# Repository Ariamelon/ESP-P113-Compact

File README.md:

# ESP-P113
 Compact version of ESP's Project 113 Amplifier done with SMT resistors and ceramic caps. PSU idea taken from https://theslowdiyer.wordpress.com/2019/09/10/project-files-filtered-irm-power-supplies-part-1/. Designed to go in sideways in this case (https://item.taobao.com/item.htm?id=54329725614). 

 ## Changelog
 ### V1
* 25/05/2021: Initial commit.
* 26/05/2021: Updated to V1.1. Added primary-side fuse, changed inductor to cheaper variant and rearranged components to make board even more compact. Updated BOM to match. Added extra M3 hole in middle of PCB and changed that hole to be the case grounding point instead.
* 27/05/2021: Updated to V1.2. Slightly changed position of transistors to allow for them to be mounted to an aluminium L-bracket and then to the case. 3mm power LEDs added. Changed output resistors to THT 0.5W versions. Added disclaimer on board. Moved position of components in CLC filter for more optimal routing.
 ### V2
* 29/05/2021: Updated to V2.0. A 220p compensation cap between opamp output and inverting input helped tame ringing on square waves with a 600R load with 10nF in parallel. A standard zobel network has also been added. Fixed major error with transistors (used wrong symbols/wrong way round, oops!). Added varistor between each power supply input and 3R resistor in series into live input, changed capacitor layout in output and added TVS diode to protect electronics in case converter fails as per CUI PSK-20D datasheet. 3.15A fuses into each live input will also be added off-board in the final design. Added gain switches to toggle gain resistance between 3k3 and 9k1 by switching 5k1 resistor in and out of parallel (actual resistance with both resistors in parallel is around 3k27, close enough), with option to choose between on-board DIP switches and off-board headers to use another switch. Output transistors changed to BD139/140. New layout, slightly larger but should still fit in planned case. Many thanks to user AnalogSteph on ASR for the help on the majority of the changes.
 ### V3
* 04/06/2021: Updated to V3.0. New layout with (hopefully) accurate measurements as drawings of case to be used have been received. Changed PSU to RAC20-15DK to save space and removed varistor. 200mA fuse will be used instead of 3.15A. Output BJTs changed to MJE15028/29s as they offer slightly better simulated distortion. The gain resistors have been changed to 560R/5k6 to allow for gain values of 1.5 and 6.6. PSU filter has been changed to CLC as that is more than adequate filtering. The DC protection and muting circuit from AMB has been added to protect the headphone out. On-board Y2 capacitor has been added for convenience. All SMT capacitors now also 1206 or 1210. Added 22kR/220pF RFI RC filter at the last second.

 ## Photos

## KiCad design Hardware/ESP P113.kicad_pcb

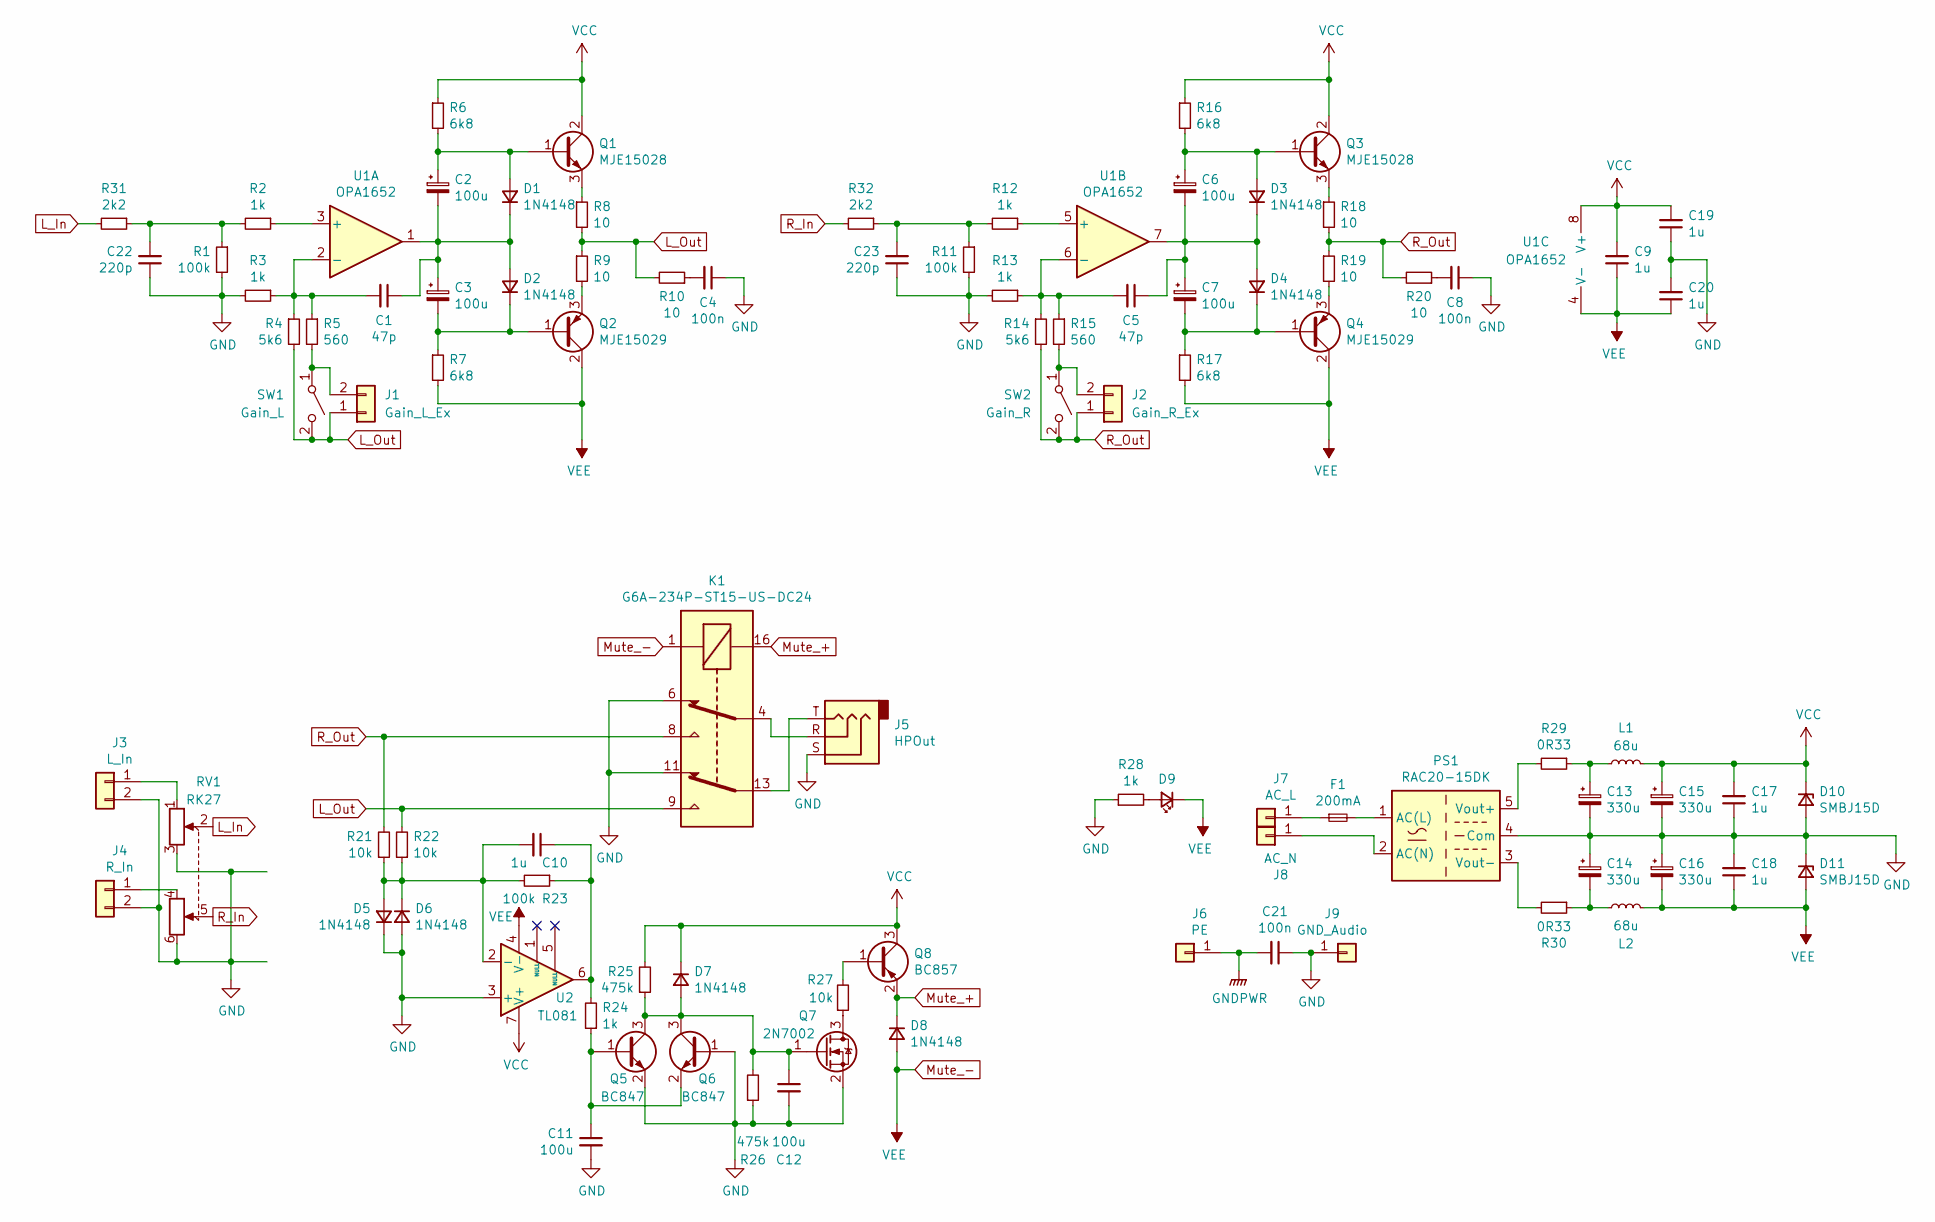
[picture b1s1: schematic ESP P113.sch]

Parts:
C1, C5: 47p; C_1206_3216Metric_Pad1.33x1.80mm_HandSolder
C2, C3, C6, C7: 100u; CP_Radial_D6.3mm_P2.50mm
C4, C8: 100n; C_1210_3225Metric_Pad1.33x2.70mm_HandSolder
C9, C17, C18, C19, C20: 1u; C_1206_3216Metric_Pad1.33x1.80mm_HandSolder
C10: 1u; C_Rect_L7.2mm_W5.5mm_P5.00mm_FKS2_FKP2_MKS2_MKP2
C11, C12: 100u; CP_Radial_D8.0mm_P3.50mm
C13, C14, C15, C16: 330u; CP_Radial_D8.0mm_P3.50mm
C21: 100n; C_Rect_L26.5mm_W8.5mm_P22.50mm_MKS4
C22, C23: 220p; C_1206_3216Metric_Pad1.33x1.80mm_HandSolder
D1, D2, D3, D4, D5, D6, D7, D8: 1N4148; D_SOD-123
D9: LED; LED_D3.0mm
D10, D11: SMBJ15D; D_SMB
F1: 200mA; Fuseholder_Cylinder-5x20mm_Schurter_0031_8201_Horizontal_Op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
J1: Gain_L_Ex; JST_XH_B2B-XH-A_1x02_P2.50mm_Vertical
J2: Gain_R_Ex; JST_XH_B2B-XH-A_1x02_P2.50mm_Vertical
J3: L_In; JST_XH_B2B-XH-A_1x02_P2.50mm_Vertical
J4: R_In; JST_XH_B2B-XH-A_1x02_P2.50mm_Vertical
J5: HPOut; Jack_6.35mm_Neutrik_NMJ6HCD2_Horizontal
J6: PE; FastOn
J7: AC_L; FastOn
J8: AC_N; FastOn
J9: GND_Audio; FastOn
K1: G6A-234P-ST15-US-DC24; Relay_DPDT_Omron_G5V-2
L1, L2: 68u; L_Radial_D8.7mm_P5.00mm_Fastron_07HCP
PS1: RAC20-15DK; Converter_ACDC_RACx0-DK_THT
Q1, Q3: MJE15028; TO-220-3_Vertical
Q2, Q4: MJE15029; TO-220-3_Vertical
Q5, Q6: BC847; SOT-23
Q7: 2N7002; SOT-23
Q8: BC857; SOT-23
R1, R11, R23: 100k; R_1206_3216Metric_Pad1.30x1.75mm_HandSolder
R2, R3, R12, R13, R24, R28: 1k; R_1206_3216Metric_Pad1.30x1.75mm_HandSolder
R4, R14: 5k6; R_1206_3216Metric_Pad1.30x1.75mm_HandSolder
R5, R15: 560; R_1206_3216Metric_Pad1.30x1.75mm_HandSolder
R6, R7, R16, R17: 6k8; R_1206_3216Metric_Pad1.30x1.75mm_HandSolder
R8, R9, R18, R19: 10; R_Axial_DIN0207_L6.3mm_D2.5mm_P7.62mm_Horizontal
R10, R20: 10; R_1206_3216Metric_Pad1.30x1.75mm_HandSolder
R21, R22, R27: 10k; R_1206_3216Metric_Pad1.30x1.75mm_HandSolder
R25, R26: 475k; R_1206_3216Metric_Pad1.30x1.75mm_HandSolder
R29, R30: 0R33; R_2512_6332Metric_Pad1.40x3.35mm_HandSolder
R31, R32: 2k2; R_1206_3216Metric_Pad1.30x1.75mm_HandSolder
RV1: RK27; ALPS_RK27112
SW1: Gain_L; SW_DIP_SPSTx01_Slide_6.7x4.1mm_W7.62mm_P2.54mm_LowProfile
SW2: Gain_R; SW_DIP_SPSTx01_Slide_6.7x4.1mm_W7.62mm_P2.54mm_LowProfile
U1: OPA1652; DIP-8_W7.62mm_Socket
U2: TL081; DIP-8_W7.62mm_Socket

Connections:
GND: C4.1, C8.1, C11.2, C12.2, C13.2, C14.1, C15.2, C16.1, C17.1, C18.2, C19.1, C20.2, C21.1, C22.1, C23.1, D5.1 (K), D6.2 (A), D10.2 (A), D11.1 (K), J3.2, J4.2, J5.S, J9.1, K1.6, K1.11, PS1.4 (Com), Q5.2 (E), Q6.1 (B), Q7.2 (S), R1.2, R3.2, R11.2, R13.2, R26.1, R28.1, RV1.3, RV1.6, U2.3 (+)
GNDPWR: C21.2, J6.1
L_In: R31.2, RV1.2
L_Out: J1.1, K1.9, R4.2, R8.2, R9.1, R10.2, R22.2, SW1.2 (B)
Mute_+: D8.1 (K), K1.16, Q8.2 (E)
Mute_-: C9.1, C16.2, C18.1, C20.1, D8.2 (A), D9.1 (K), D11.2 (A), K1.1, L2.2, Q2.2 (C), Q4.2 (C), R7.2, R17.2, U1.4 (V-), U2.4 (V-)
unnamed: C1.1, C2.2, C3.1, D1.1 (K), D2.2 (A), U1.1
unnamed: C1.2, R3.1, R4.1, R5.1, U1.2 (-)
unnamed: C2.1, D1.2 (A), Q1.1 (B), R6.2
unnamed: C3.2, D2.1 (K), Q2.1 (B), R7.1
unnamed: C4.2, R10.1
unnamed: C5.1, C6.2, C7.1, D3.1 (K), D4.2 (A), U1.7
unnamed: C5.2, R13.1, R14.1, R15.1, U1.6 (-)
unnamed: C6.1, D3.2 (A), Q3.1 (B), R16.2
unnamed: C7.2, D4.1 (K), Q4.1 (B), R17.1
unnamed: C8.2, R20.1
unnamed: C10.1, R23.1, R24.2, U2.6
unnamed: C10.2, D5.2 (A), D6.1 (K), R21.1, R22.1, R23.2, U2.2 (-)
unnamed: C11.1, Q5.1 (B), Q6.2 (E), R24.1
unnamed: C12.1, D7.2 (A), Q5.3 (C), Q6.3 (C), Q7.1 (G), R25.1, R26.2
unnamed: C13.1, L1.1, R29.1
unnamed: C14.2, L2.1, R30.1
unnamed: C22.2, R1.1, R2.2, R31.1
unnamed: C23.2, R11.1, R12.2, R32.1
unnamed: D9.2 (A), R28.2
unnamed: F1.1, J7.1
unnamed: F1.2, PS1.1 (AC(L))
unnamed: J1.2, R5.2, SW1.1 (A)
unnamed: J2.2, R15.2, SW2.1 (A)
unnamed: J3.1, RV1.1
unnamed: J4.1, RV1.4
unnamed: J5.R, K1.4
unnamed: J5.T, K1.13
unnamed: J8.1, PS1.2 (AC(N))
unnamed: PS1.3 (Vout-), R30.2
unnamed: PS1.5 (Vout+), R29.2
unnamed: Q1.3 (E), R8.1
unnamed: Q2.3 (E), R9.2
unnamed: Q3.3 (E), R18.1
unnamed: Q4.3 (E), R19.2
unnamed: Q7.3 (D), R27.1
unnamed: Q8.1 (B), R27.2
unnamed: R2.1, U1.3 (+)
unnamed: R12.1, U1.5 (+)
R_In: R32.2, RV1.5
R_Out: J2.1, K1.8, R14.2, R18.2, R19.1, R20.2, R21.2, SW2.2 (B)
VCC: C9.2, C15.1, C17.2, C19.2, D7.1 (K), D10.1 (K), L1.2, Q1.2 (C), Q3.2 (C), Q8.3 (C), R6.1, R16.1, R25.2, U1.8 (V+), U2.7 (V+)

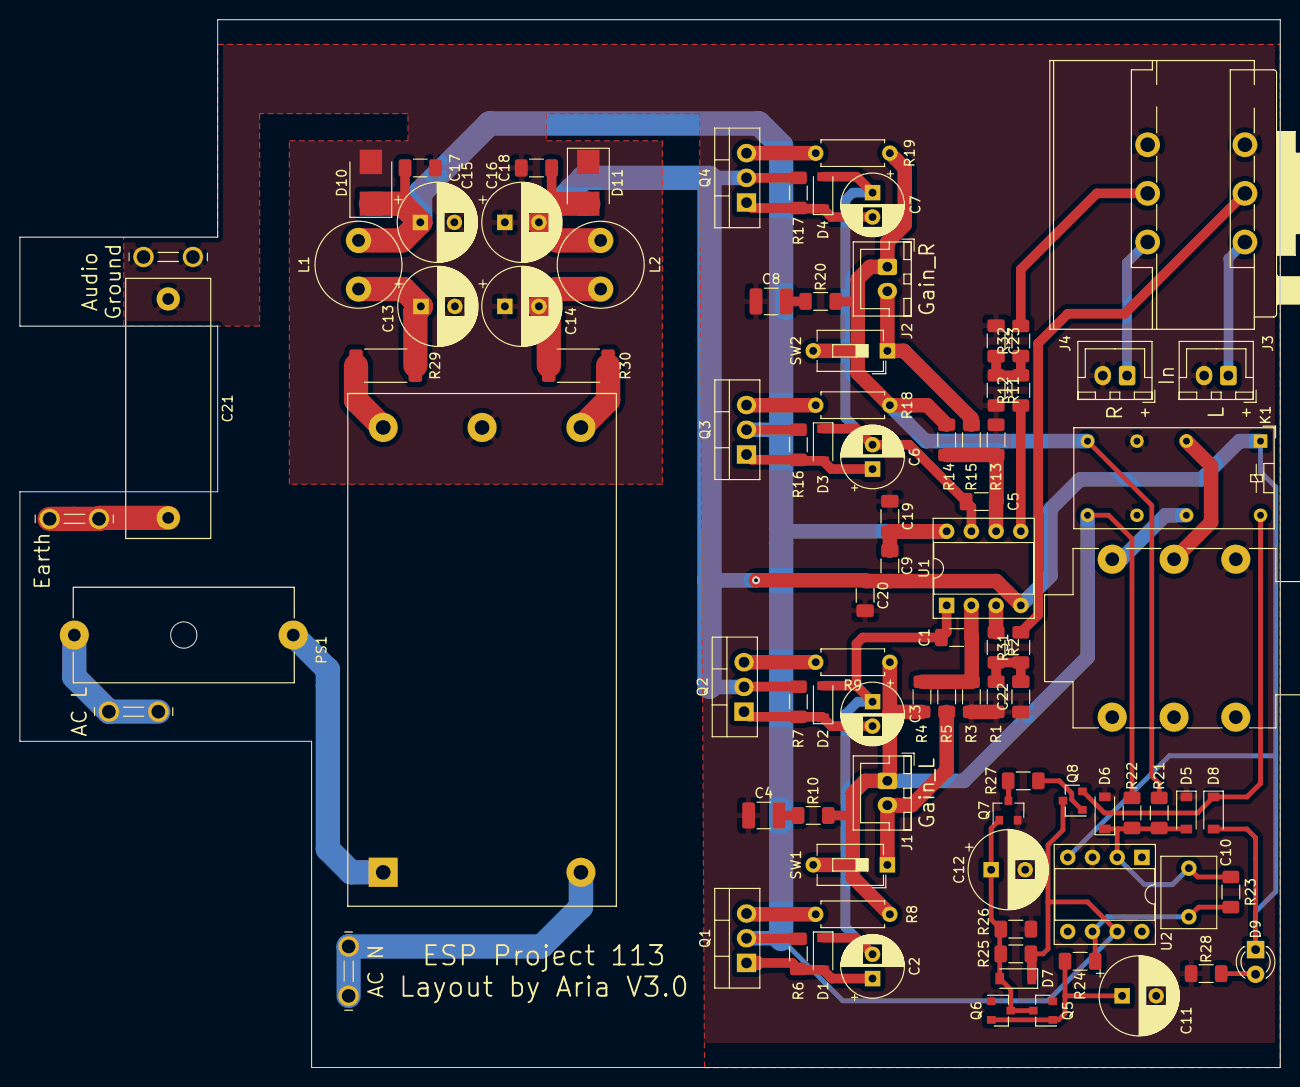
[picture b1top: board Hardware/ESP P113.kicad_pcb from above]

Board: 2 copper layers, 129.5 x 107.6 mm, 93 parts (0 on the bottom side), 47 nets.

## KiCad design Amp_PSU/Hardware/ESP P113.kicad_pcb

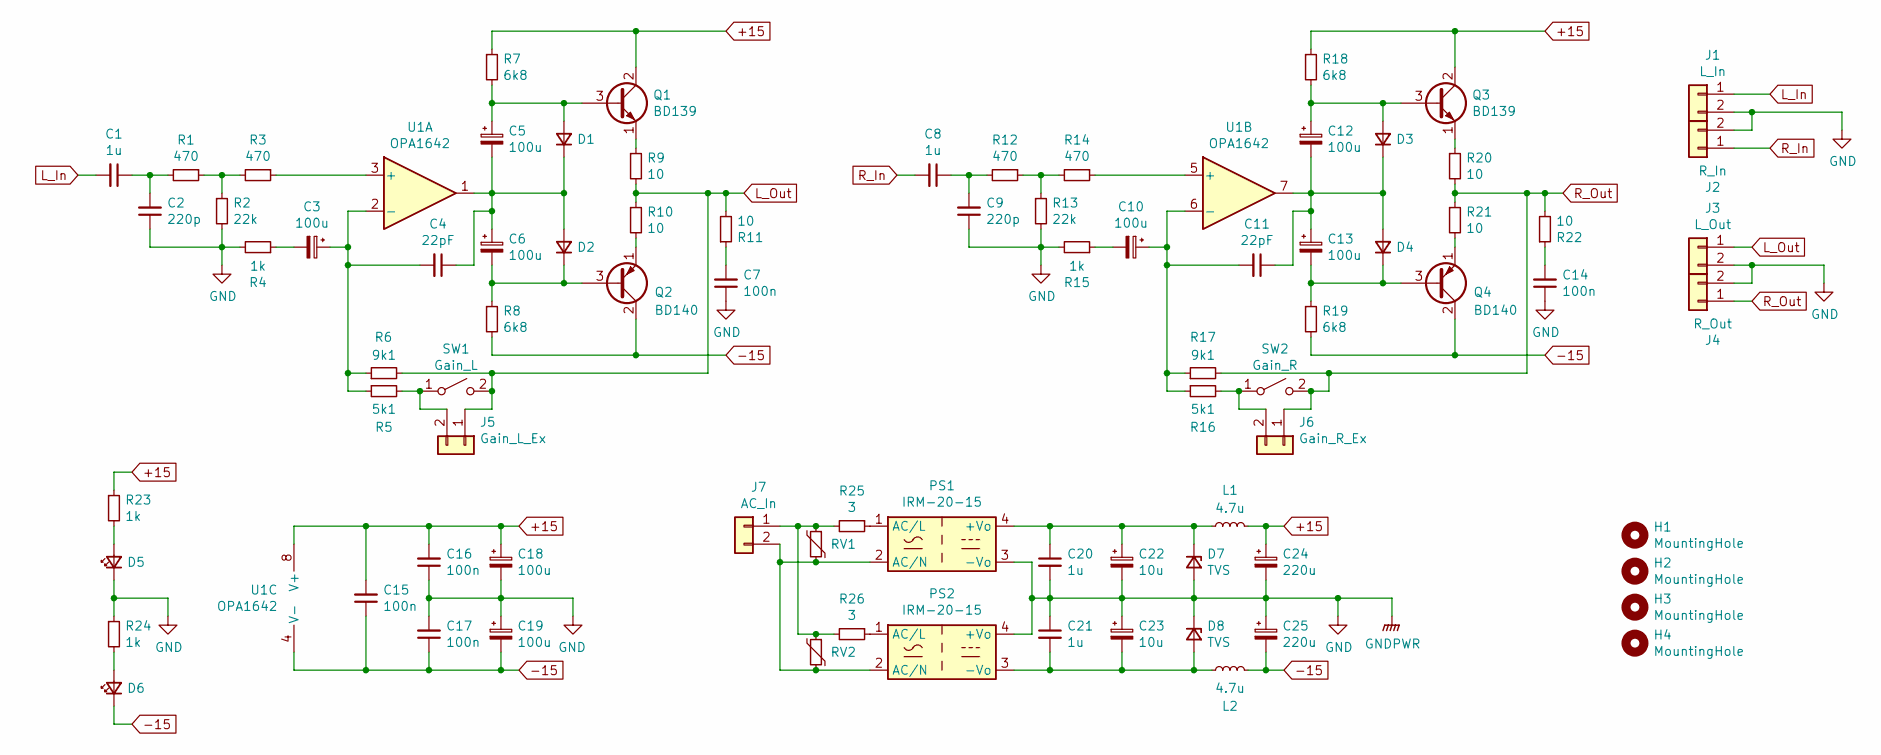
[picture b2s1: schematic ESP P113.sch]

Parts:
C1, C8: 1u; C_Rect_L18.0mm_W5.0mm_P15.00mm_FKS3_FKP3
C2, C9: 220p; C_0805_2012Metric_Pad1.15x1.40mm_HandSolder
C3, C5, C6, C10, C12, C13, C18, C19: 100u; CP_Radial_D6.3mm_P2.50mm
C4, C11: 22pF; C_0805_2012Metric_Pad1.15x1.40mm_HandSolder
C7, C14, C15, C16, C17: 100n; C_0805_2012Metric_Pad1.15x1.40mm_HandSolder
C20, C21: 1u; C_0805_2012Metric_Pad1.15x1.40mm_HandSolder
C22, C23: 10u; CP_Radial_D6.3mm_P2.50mm
C24, C25: 220u; CP_Radial_D8.0mm_P3.50mm
D1, D2, D3, D4: 1n4148; D_SOD-123
D5, D6: LED; LED_D3.0mm
D7, D8: TVS; D_SMB
H1, H2, H3, H4: MountingHole; MountingHole_3.2mm_M3_Pad_Via
J1: L_In; JST_XH_B2B-XH-A_1x02_P2.50mm_Vertical
J2: R_In; JST_XH_B2B-XH-A_1x02_P2.50mm_Vertical
J3: L_Out; JST_XH_B2B-XH-A_1x02_P2.50mm_Vertical
J4: R_Out; JST_XH_B2B-XH-A_1x02_P2.50mm_Vertical
J5: Gain_L_Ex; JST_XH_B2B-XH-A_1x02_P2.50mm_Vertical
J6: Gain_R_Ex; JST_XH_B2B-XH-A_1x02_P2.50mm_Vertical
J7: AC_In; MountingHole_3.2mm_M3_Pad_Via
L1, L2: 4.7u; L_Taiyo-Yuden_NR-80xx_HandSoldering
PS1, PS2: IRM-20-15; Converter_ACDC_MeanWell_IRM-20-xx_THT
Q1, Q3: BD139; TO-126-3_Vertical
Q2, Q4: BD140; TO-126-3_Vertical
R1, R3, R12, R14: 470; R_1206_3216Metric_Pad1.42x1.75mm_HandSolder
R2, R13: 22k; R_1206_3216Metric_Pad1.42x1.75mm_HandSolder
R4, R15, R23, R24: 1k; R_1206_3216Metric_Pad1.42x1.75mm_HandSolder
R5, R16: 5k1; R_1206_3216Metric_Pad1.42x1.75mm_HandSolder
R6, R17: 9k1; R_1206_3216Metric_Pad1.42x1.75mm_HandSolder
R7, R8, R18, R19: 6k8; R_1206_3216Metric_Pad1.42x1.75mm_HandSolder
R9, R10, R20, R21: 10; R_Axial_DIN0207_L6.3mm_D2.5mm_P7.62mm_Horizontal
R11, R22: 10; R_1206_3216Metric_Pad1.42x1.75mm_HandSolder
R25, R26: 3; R_Axial_DIN0614_L14.3mm_D5.7mm_P15.24mm_Horizontal
RV1, RV2: MOV; C_Disc_D14.5mm_W5.0mm_P7.50mm
SW1: Gain_L; SW_DIP_SPSTx01_Slide_6.7x4.1mm_W7.62mm_P2.54mm_LowProfile
SW2: Gain_R; SW_DIP_SPSTx01_Slide_6.7x4.1mm_W7.62mm_P2.54mm_LowProfile
U1: OPA1642; DIP-8_W7.62mm_Socket

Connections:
+15: C15.2, C16.2, C18.1, C24.1, L1.2, Q1.2 (C), Q3.2 (C), R7.1, R18.1, R23.1, U1.8 (V+)
-15: C15.1, C17.1, C19.2, C25.2, D6.1 (K), L2.2, Q2.2 (C), Q4.2 (C), R8.2, R19.2, U1.4 (V-)
GND: C2.1, C7.1, C9.1, C14.1, C16.1, C17.2, C18.2, C19.1, C20.2, C21.1, C22.2, C23.1, C24.2, C25.1, D5.1 (K), D7.2 (A), D8.1 (K), J1.2, J2.2, J3.2, J4.2, PS1.3 (-Vo), PS2.4 (+Vo), R2.2, R4.2, R13.2, R15.2, R24.1
L_In: C1.2, J1.1
L_Out: J3.1, J5.1, R6.2, R9.2, R10.1, R11.2, SW1.2 (B)
unnamed: C1.1, C2.2, R1.2
unnamed: C3.1, C4.2, R5.1, R6.1, U1.2 (-)
unnamed: C3.2, R4.1
unnamed: C4.1, C5.2, C6.1, D1.1 (K), D2.2 (A), U1.1
unnamed: C5.1, D1.2 (A), Q1.3 (B), R7.2
unnamed: C6.2, D2.1 (K), Q2.3 (B), R8.1
unnamed: C7.2, R11.1
unnamed: C8.1, C9.2, R12.2
unnamed: C10.1, C11.2, R16.1, R17.1, U1.6 (-)
unnamed: C10.2, R15.1
unnamed: C11.1, C12.2, C13.1, D3.1 (K), D4.2 (A), U1.7
unnamed: C12.1, D3.2 (A), Q3.3 (B), R18.2
unnamed: C13.2, D4.1 (K), Q4.3 (B), R19.1
unnamed: C14.2, R22.1
unnamed: C20.1, C22.1, D7.1 (K), L1.1, PS1.4 (+Vo)
unnamed: C21.2, C23.2, D8.2 (A), L2.1, PS2.3 (-Vo)
unnamed: D5.2 (A), R23.2
unnamed: D6.2 (A), R24.2
unnamed: J5.2, R5.2, SW1.1 (A)
unnamed: J6.2, R16.2, SW2.1 (A)
unnamed: J7.1, R25.2, R26.2, RV1.1, RV2.1
unnamed: J7.2, PS1.2 (AC/N), PS2.2 (AC/N), RV1.2, RV2.2
unnamed: PS1.1 (AC/L), R25.1
unnamed: PS2.1 (AC/L), R26.1
unnamed: Q1.1 (E), R9.1
unnamed: Q2.1 (E), R10.2
unnamed: Q3.1 (E), R20.1
unnamed: Q4.1 (E), R21.2
unnamed: R1.1, R2.1, R3.2
unnamed: R3.1, U1.3 (+)
unnamed: R12.1, R13.1, R14.2
unnamed: R14.1, U1.5 (+)
R_In: C8.2, J2.1
R_Out: J4.1, J6.1, R17.2, R20.2, R21.1, R22.2, SW2.2 (B)

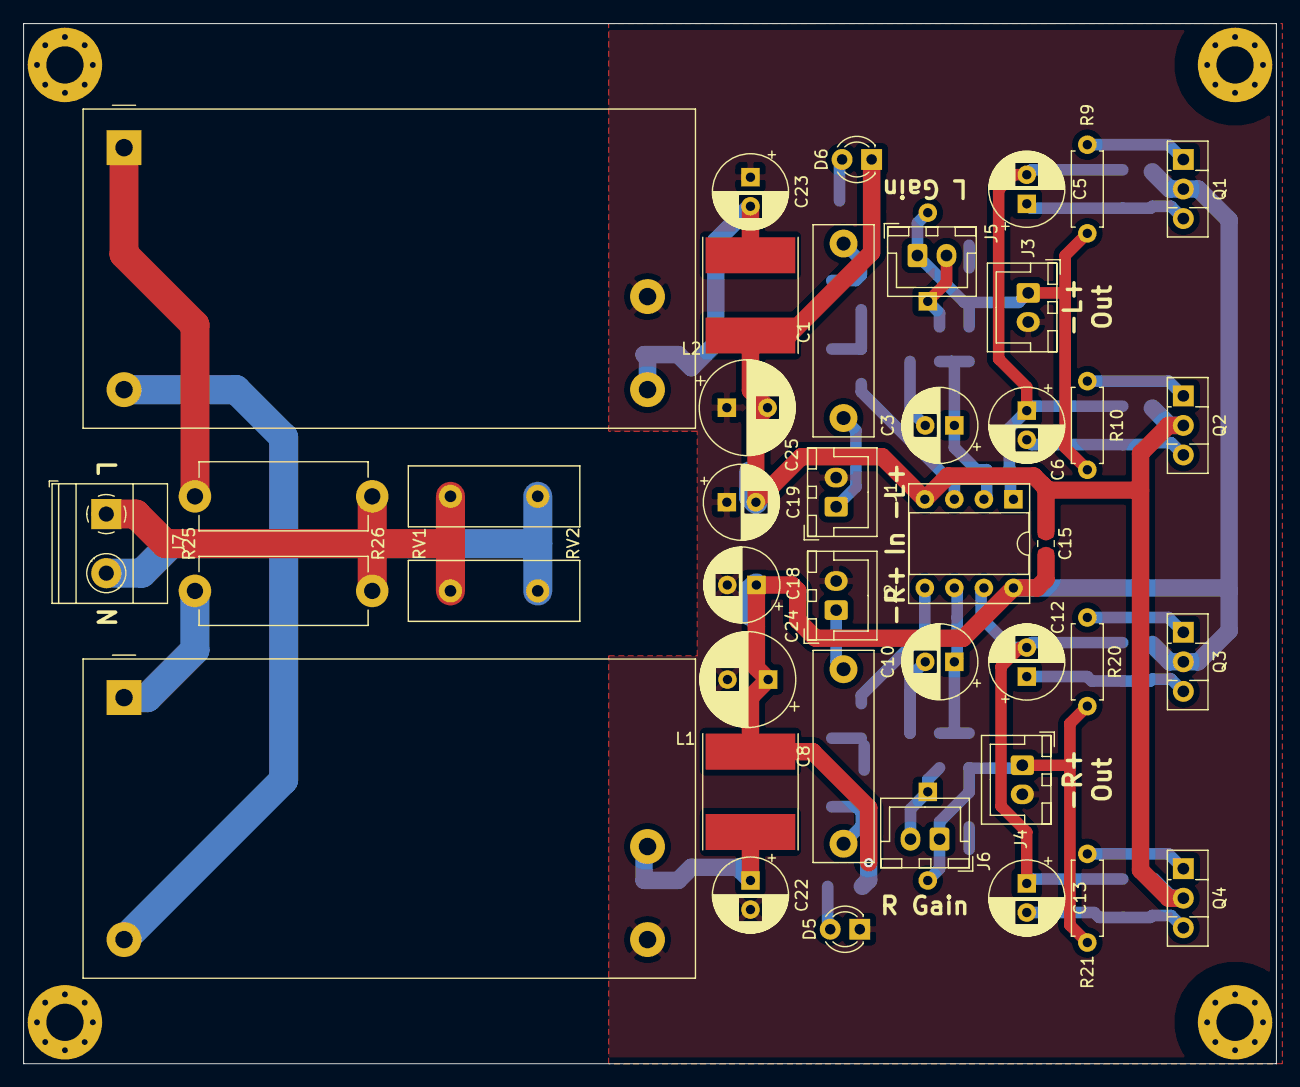
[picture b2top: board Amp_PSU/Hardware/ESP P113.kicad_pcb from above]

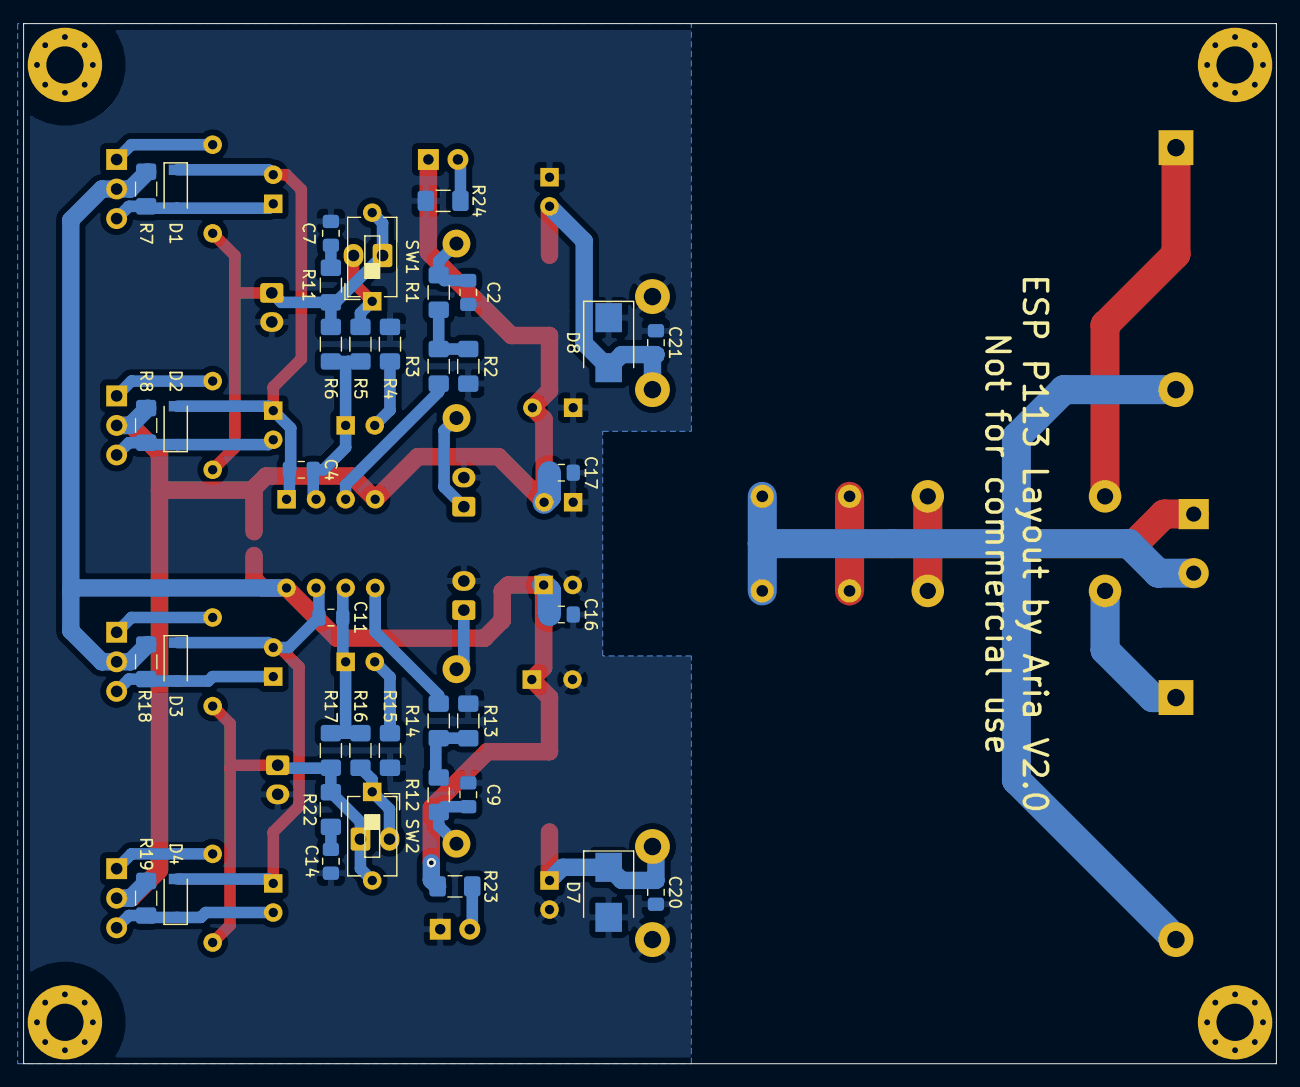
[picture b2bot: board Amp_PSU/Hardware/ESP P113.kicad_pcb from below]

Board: 2 copper layers, 107.7 x 89.4 mm, 83 parts (38 on the bottom side), 39 nets.

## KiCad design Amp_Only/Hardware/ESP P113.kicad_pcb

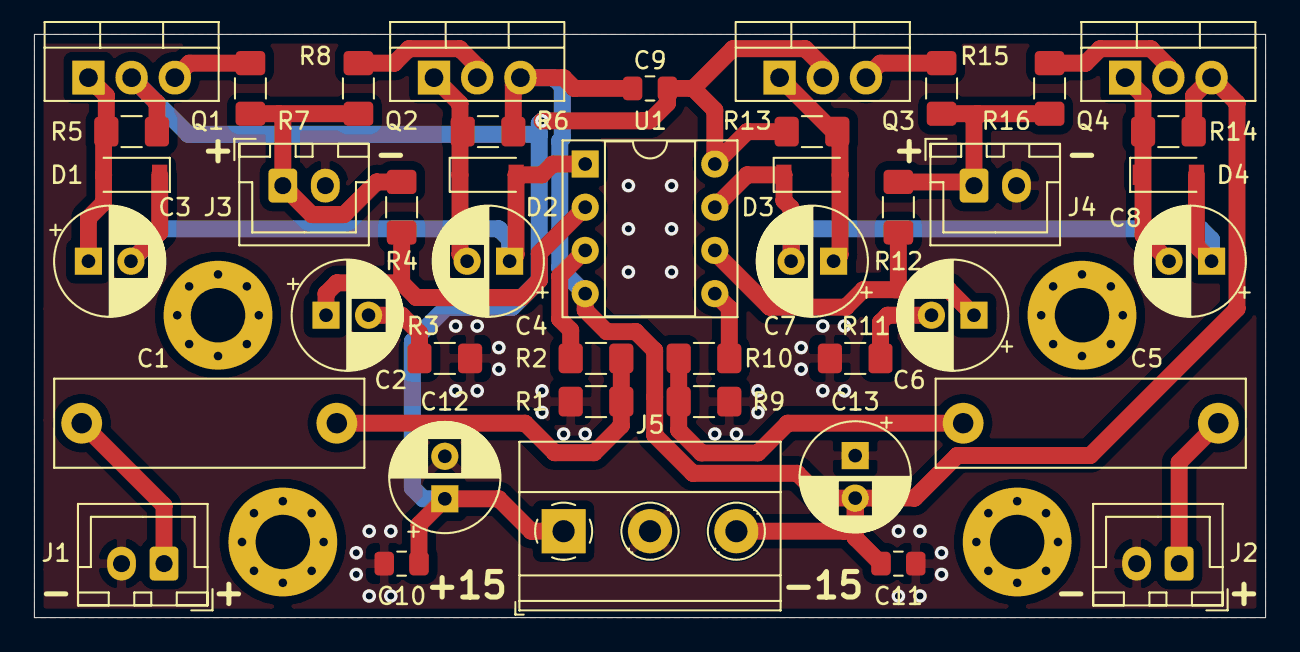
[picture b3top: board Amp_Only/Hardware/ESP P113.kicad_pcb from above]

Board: 2 copper layers, 72.4 x 34.3 mm, 47 parts (0 on the bottom side), 25 nets.

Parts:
C1, C5: 1u; C_Rect_L18.0mm_W5.0mm_P15.00mm_FKS3_FKP3
C2, C3, C4, C6, C7, C8, C12, C13: 100u; CP_Radial_D6.3mm_P2.50mm
C9, C10, C11: 100n; C_0805_2012Metric_Pad1.15x1.40mm_HandSolder
D1, D2, D3, D4: 1n4148; D_SOD-123
H1, H2, H3, H4: MountingHole; MountingHole_3.2mm_M3_Pad_Via
J1: L_In; JST_XH_B2B-XH-A_1x02_P2.50mm_Vertical
J2: R_In; JST_XH_B2B-XH-A_1x02_P2.50mm_Vertical
J3: L_Out; JST_XH_B2B-XH-A_1x02_P2.50mm_Vertical
J4: R_Out; JST_XH_B2B-XH-A_1x02_P2.50mm_Vertical
J5: DC_In; TerminalBlock_Phoenix_MKDS-1,5-3-5.08_1x03_P5.08mm_Horizont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
Q1, Q3: MJE15032; TO-220-3_Vertical
Q2, Q4: MJE15033; TO-220-3_Vertical
R1, R9: 22k; R_1206_3216Metric_Pad1.42x1.75mm_HandSolder
R2, R3, R10, R11: 1k; R_1206_3216Metric_Pad1.42x1.75mm_HandSolder
R4, R12: 3k3; R_1206_3216Metric_Pad1.42x1.75mm_HandSolder
R5, R6, R13, R14: 6k8; R_1206_3216Metric_Pad1.42x1.75mm_HandSolder
R7, R8, R15, R16: 10; R_1206_3216Metric_Pad1.42x1.75mm_HandSolder
U1: LM4562; DIP-8_W7.62mm_Socket

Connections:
+15: C9.2, C10.2, C12.1, J5.1, Q1.2, Q3.2, R5.1, R13.1, U1.8
-15: C9.1, C11.1, C13.2, J5.3, Q2.3, Q4.3, R6.2, R14.2, U1.4
GND: C10.1, C11.2, C12.2, C13.1, J1.2, J2.2, J3.2, J4.2, J5.2, R1.2, R3.2, R9.2, R11.2
L_In: C1.2, J1.1
L_Out: J3.1, R4.2, R7.2, R8.1
unnamed: C1.1, R1.1, R2.2
unnamed: C2.1, R4.1, U1.2
unnamed: C2.2, R3.1
unnamed: C3.1, D1.2, Q1.1, R5.2
unnamed: C3.2, C4.1, D1.1, D2.2, U1.1
unnamed: C4.2, D2.1, Q2.1, R6.1
unnamed: C5.1, R9.1, R10.2
unnamed: C6.1, R12.1, U1.6
unnamed: C6.2, R11.1
unnamed: C7.1, D3.2, Q3.1, R13.2
unnamed: C7.2, C8.1, D3.1, D4.2, U1.7
unnamed: C8.2, D4.1, Q4.1, R14.1
unnamed: Q1.3, R7.1
unnamed: Q2.2, R8.2
unnamed: Q3.3, R15.1
unnamed: Q4.2, R16.2
unnamed: R2.1, U1.3
unnamed: R10.1, U1.5
R_In: C5.2, J2.1
R_Out: J4.1, R12.2, R15.2, R16.1

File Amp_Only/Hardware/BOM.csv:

Ref,Qnty,Value,Mfr. No,Package
"C1, C5",2,1u,ECW-FE2W105JA,"18 x 5mm PP film cap, 15mm pin pacing"
"C2, C3, C4, C6, C7, C8, C12, C13",8,100u,EEU-FC1E101SB,"6.3mm diameter radial electrolytic, 2.5mm pin spacing"
"C9, C10, C11",3,100n,GCM21BR72A104KA37L,0805 X7R capacitor
"D1, D2, D3, D4",4,,1N4148W-7-F,SOD-123 SMT diode
"D5, D6",2,,LTL-4222,3mm LED
"J1, J2, J3, J4",4,,B2B-XH-A(LF)(SN),2 position 2.54mm spacing XH2P JST connector
J5,1,,1715035,3 position 5.08mm spacing phoenix terminal block
"Q1, Q3",2,MJE15032,MJE15032G,TO-220 NPN BJT
"Q2, Q4",2,MJE15033,MJE15033G,TO-220 PNP BJT
"R1, R9",2,22k,RT1206FRE0722KL,1206 thin film resistor
"R2, R3, R10, R11, R17, R18",6,1k,RT1206FRE071KL,1206 thin film resistor
"R4, R12",2,3k3,RT1206FRE073K3L,1206 thin film resistor
"R5, R6, R13, R14",4,6k8,RT1206FRE076K8L,1206 thin film resistor
"R7, R8, R15, R16",4,10,RT1206FRE0710RL,1206 thin film resistor
U1,1,LM4562,LM4562NA/NOPB,DIP-8 opamp

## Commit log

2021-05-25 Deleted old BOM and added images to readme
2021-05-26 Updated to V1.1
2021-05-26 Removed ground plane from PSU area
2021-05-26 Updated to V1.2.
2021-05-27 Added version with no PSU
2021-05-27 Fixed image links, updated BOM
2021-05-27 Fixed amp only schematic
2021-05-27 Slightly moved position of output resistors.
2021-05-27 Revert "Slightly moved position of output resistors."
    This reverts commit 2c67a83915dd1cff94a26fcd4de2be662b6489d6.
2021-05-27 Changed output resistors to THT 0.5W versions. Removed amp-only version. Added disclaimer on board.
2021-05-27 Moved position of components in CLC filter for more optimal routing.
2021-05-28 Updated to V2.0.
2021-05-29 Changed layout
2021-05-29 Minor correction
2021-06-04 Updated to V3.0.
2021-06-04 Fixed readme
2021-06-04 Updated layout, re-added BOM.
2021-06-04 Added RFI filter.
2021-06-04 Updated BOM.
